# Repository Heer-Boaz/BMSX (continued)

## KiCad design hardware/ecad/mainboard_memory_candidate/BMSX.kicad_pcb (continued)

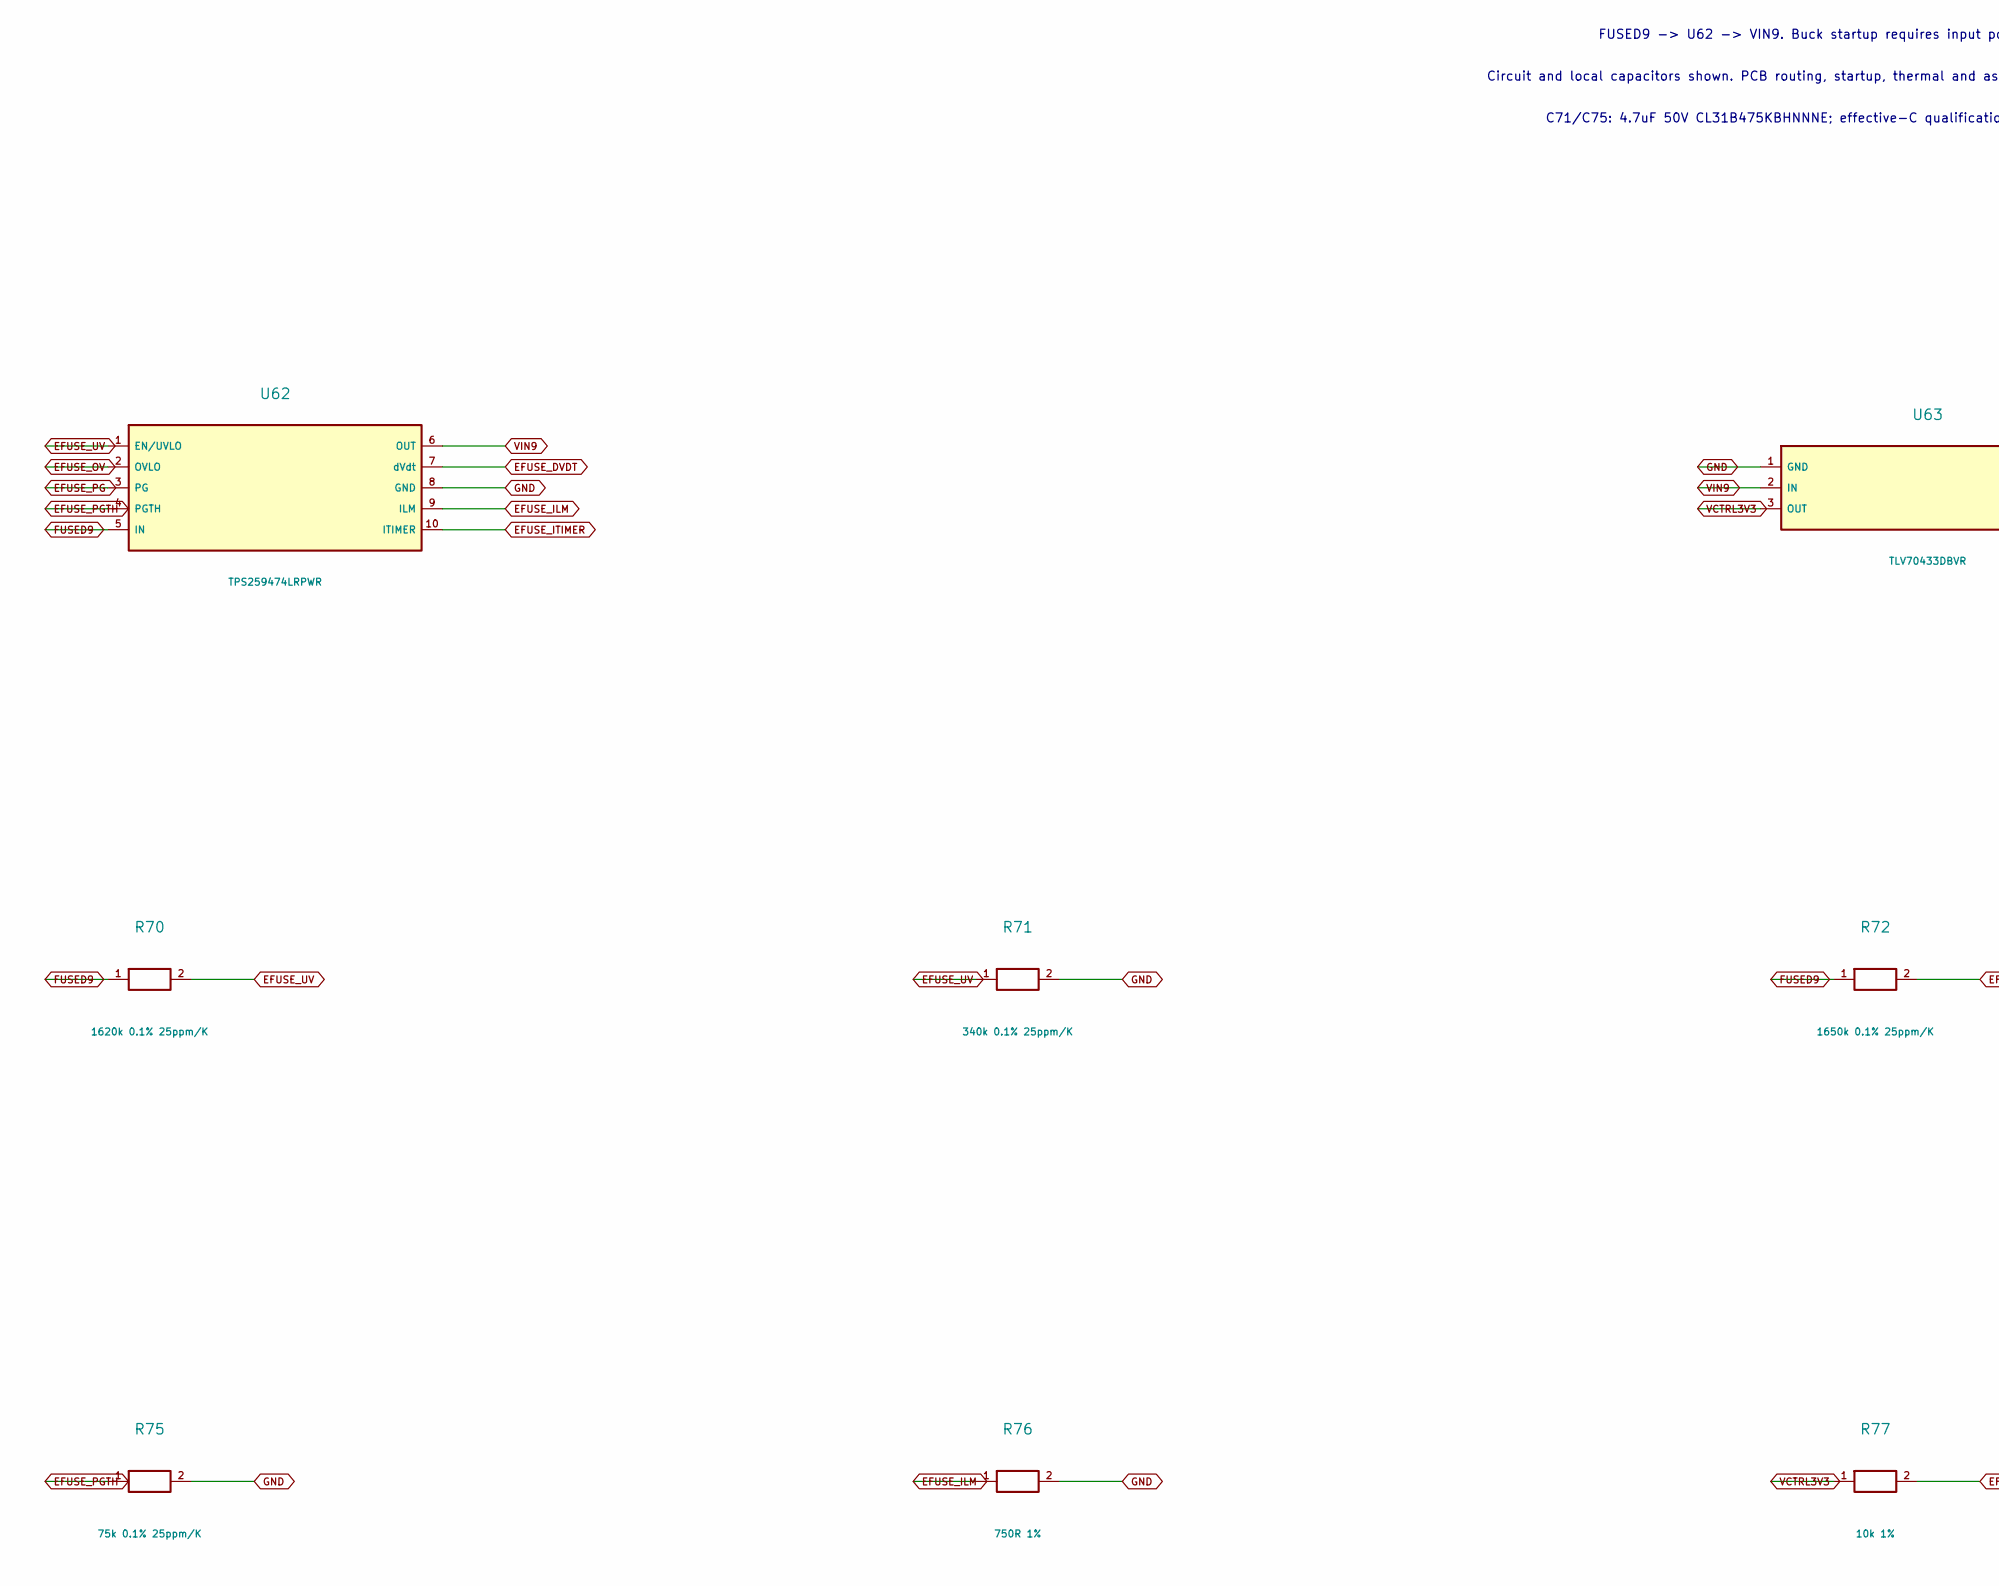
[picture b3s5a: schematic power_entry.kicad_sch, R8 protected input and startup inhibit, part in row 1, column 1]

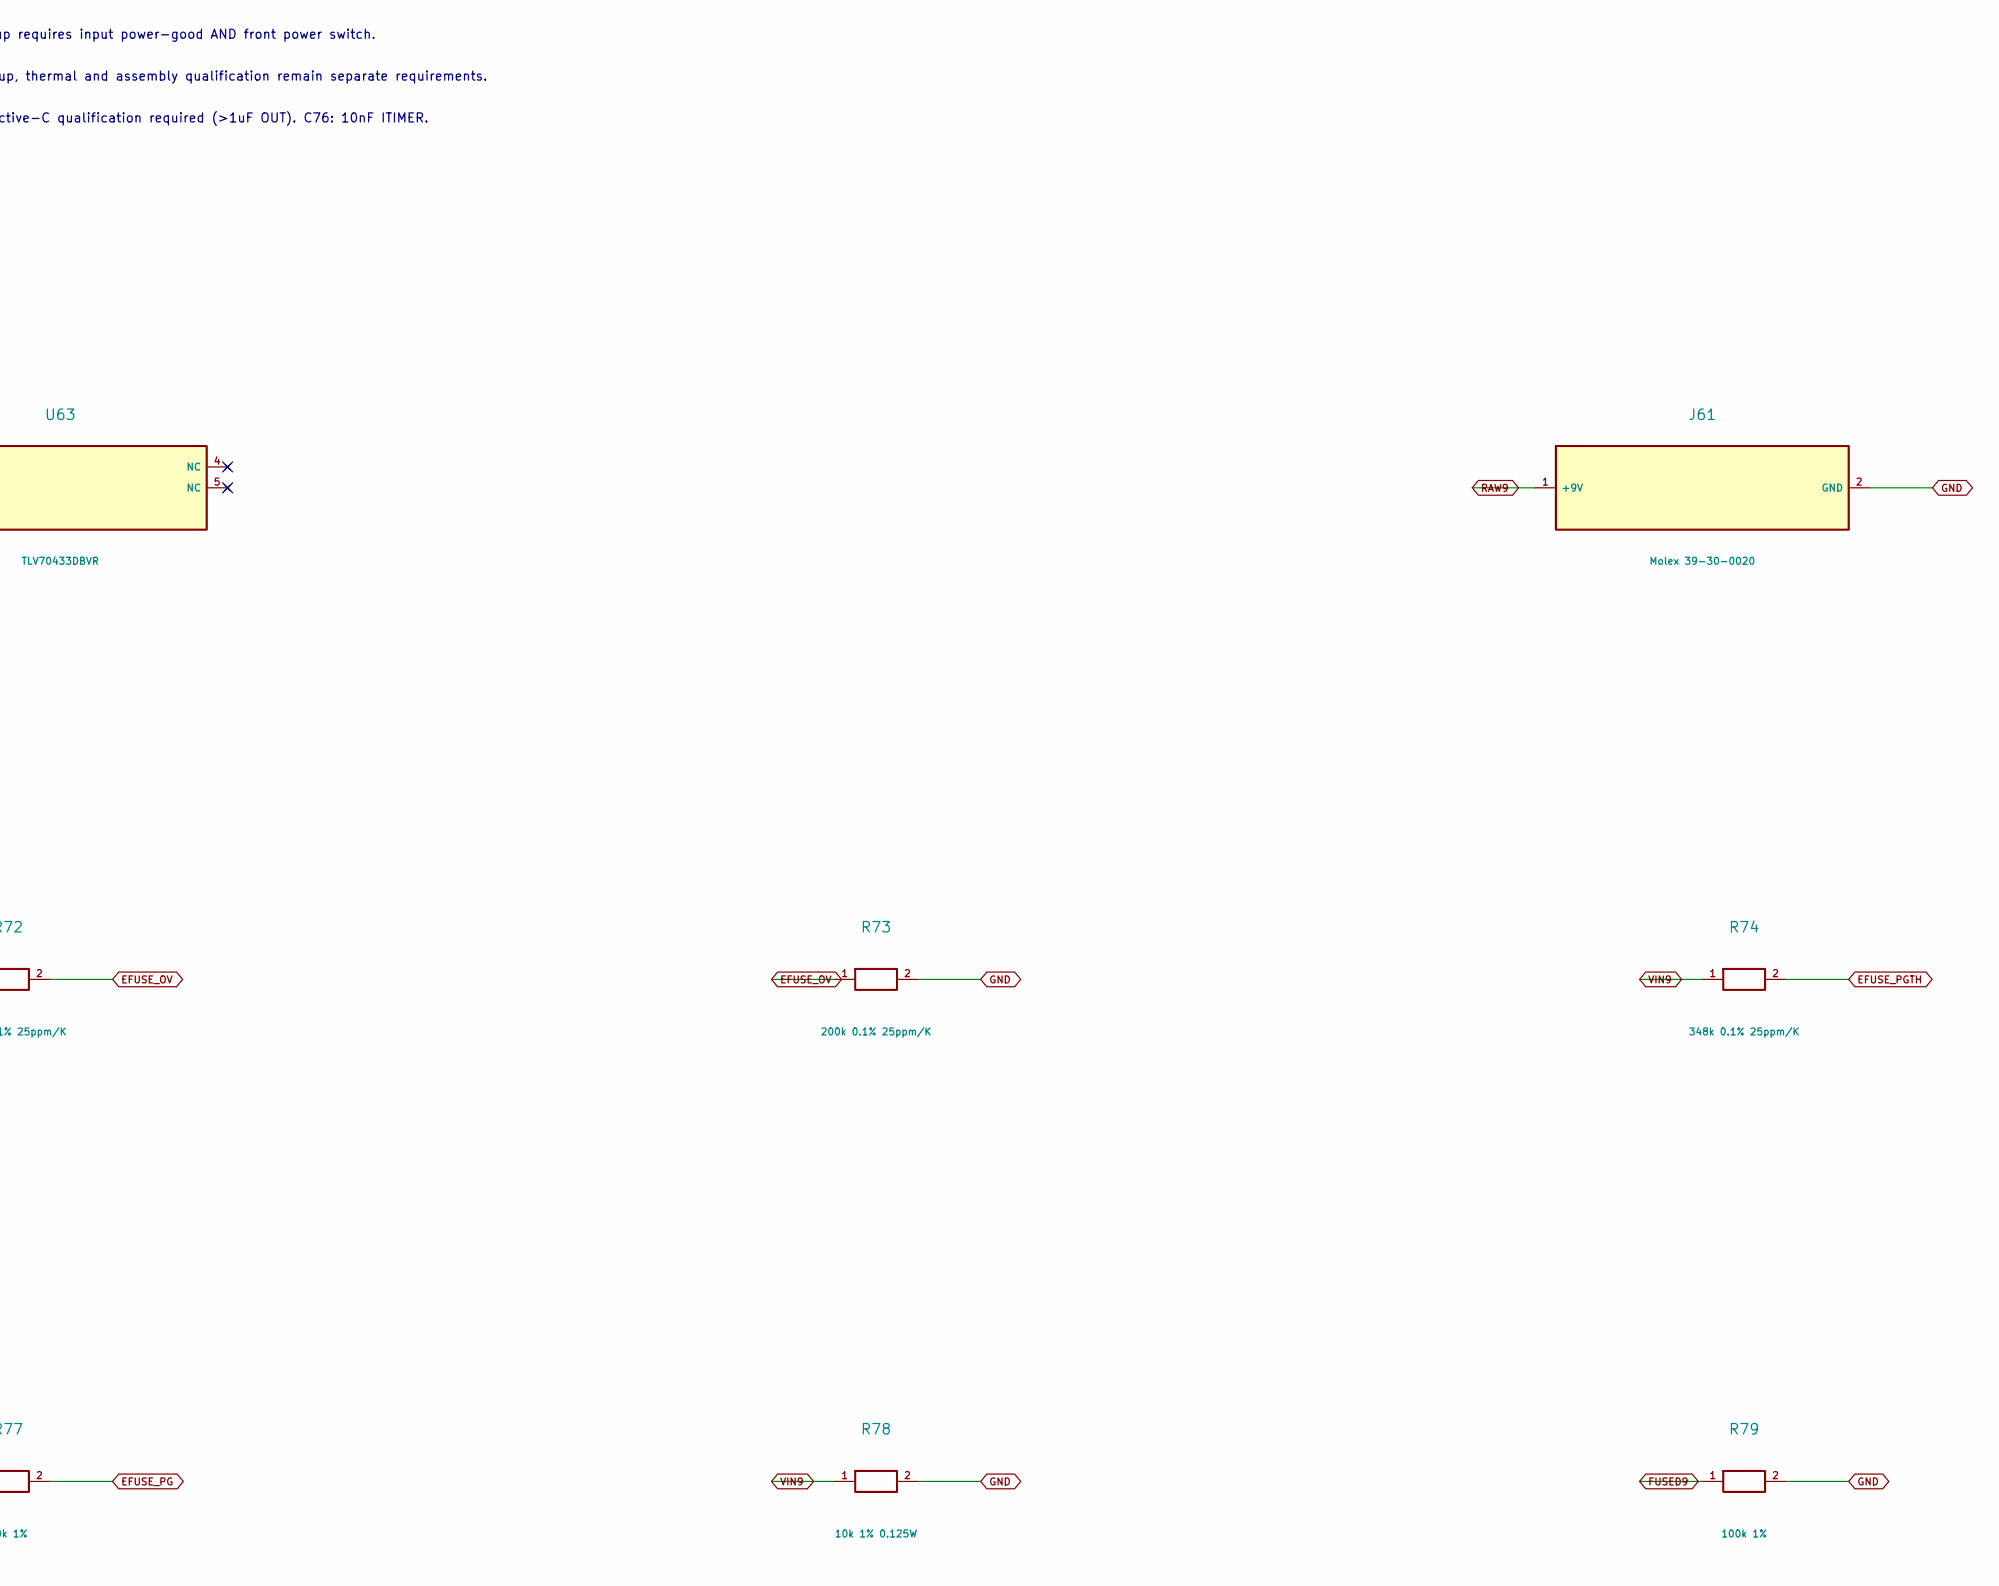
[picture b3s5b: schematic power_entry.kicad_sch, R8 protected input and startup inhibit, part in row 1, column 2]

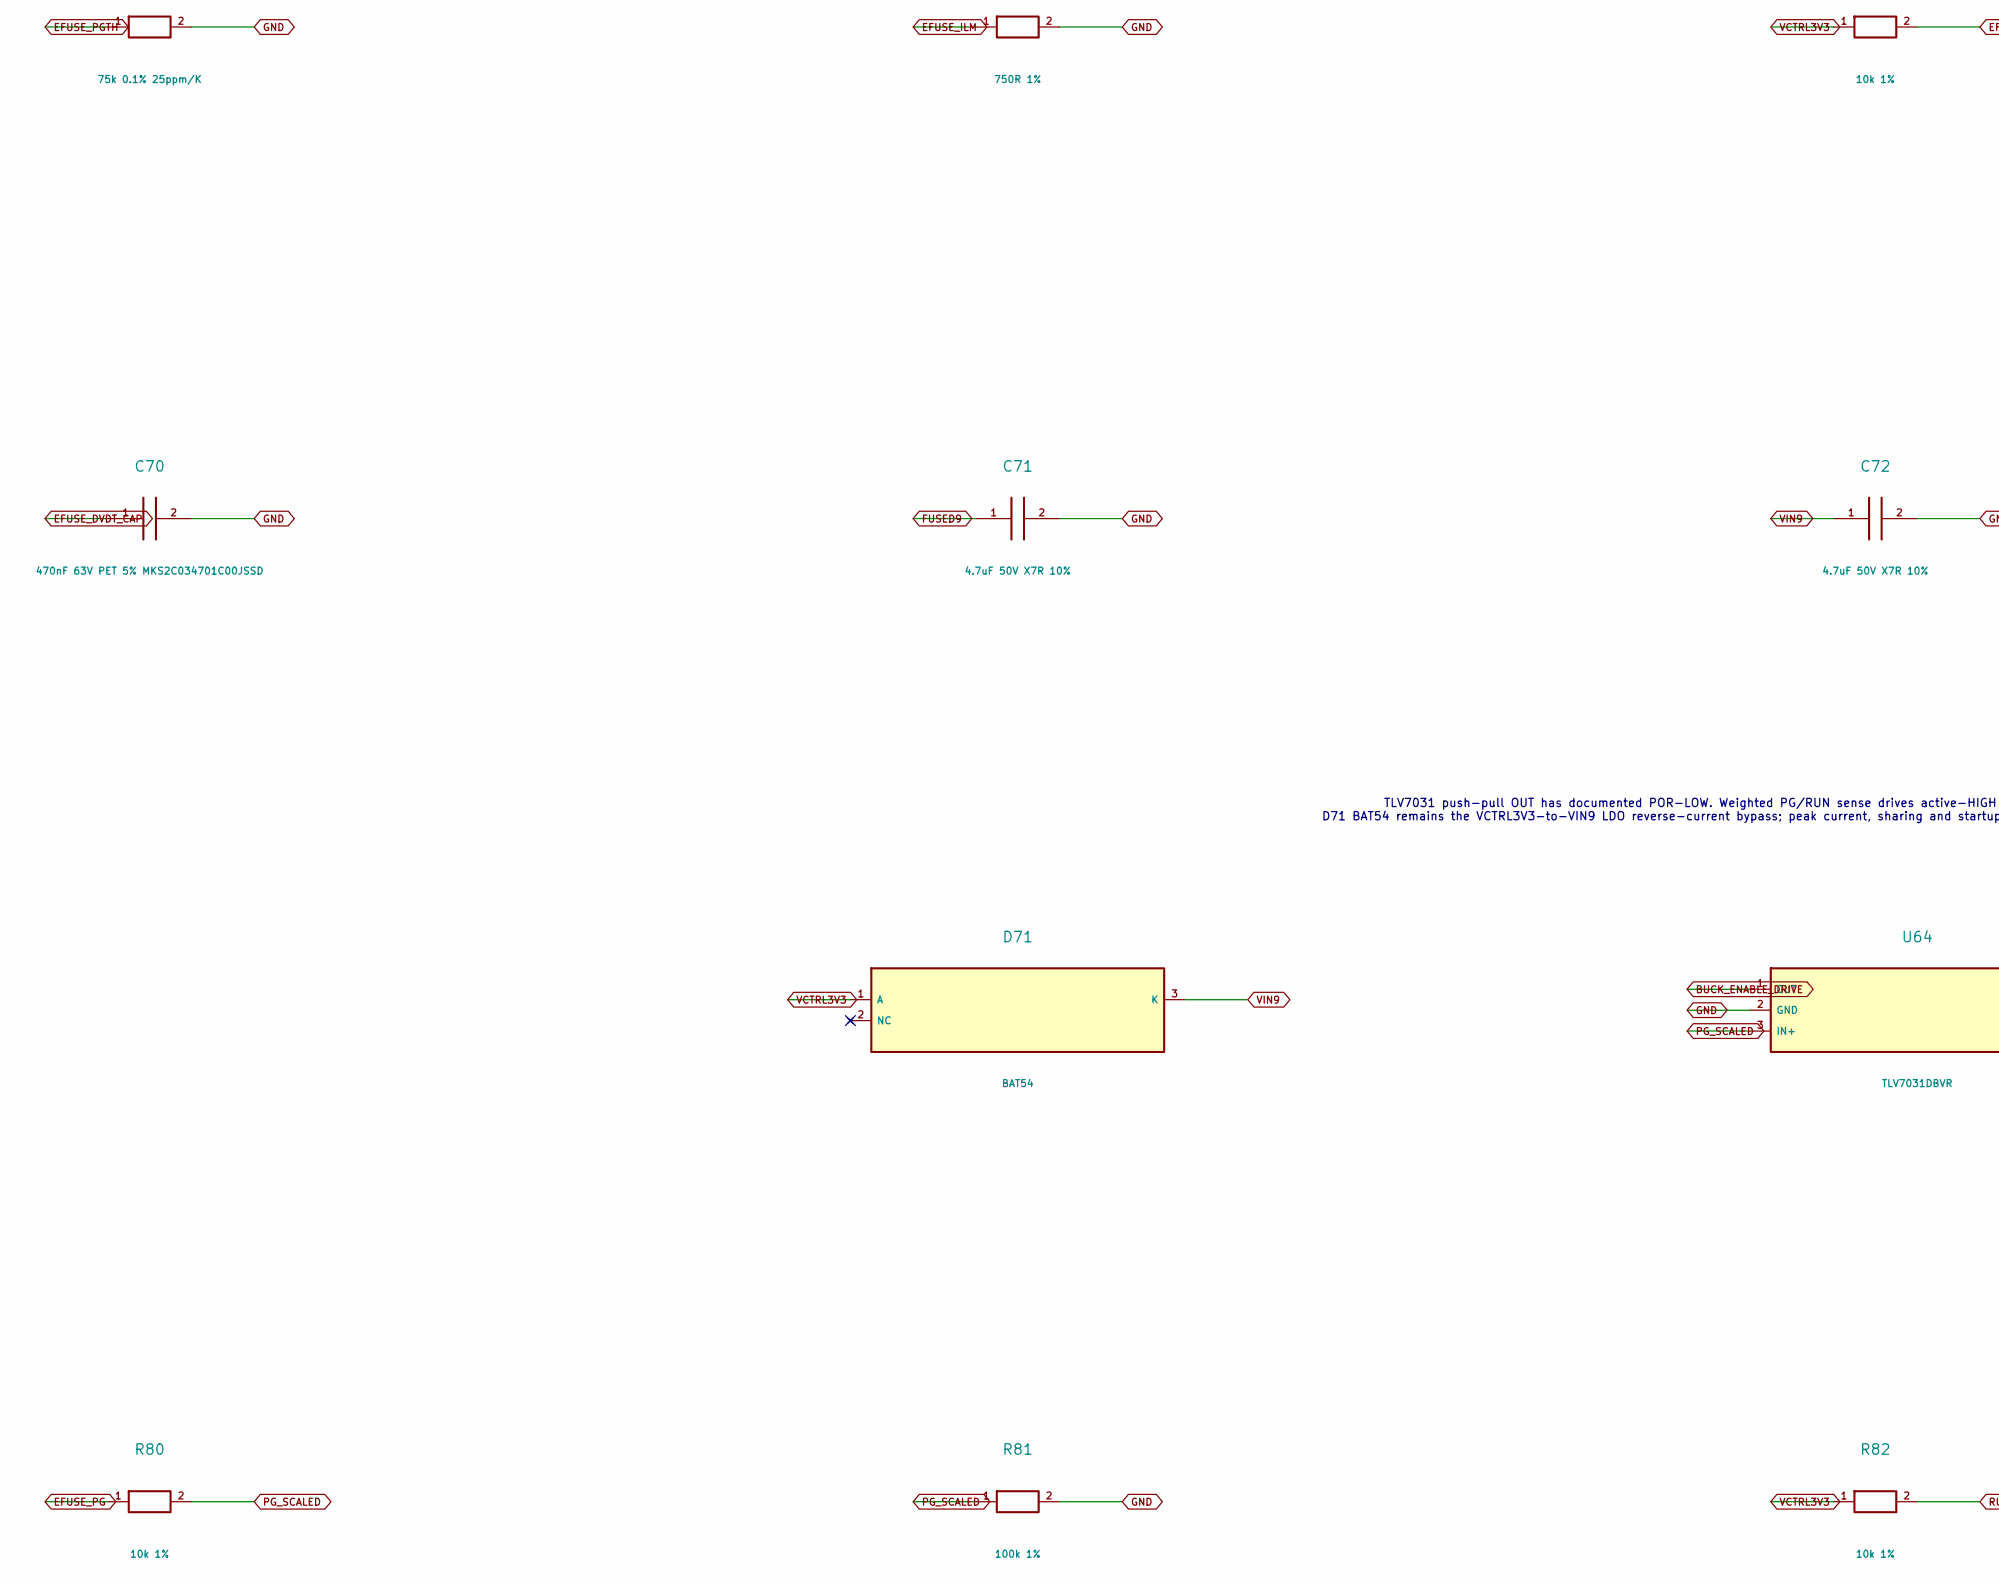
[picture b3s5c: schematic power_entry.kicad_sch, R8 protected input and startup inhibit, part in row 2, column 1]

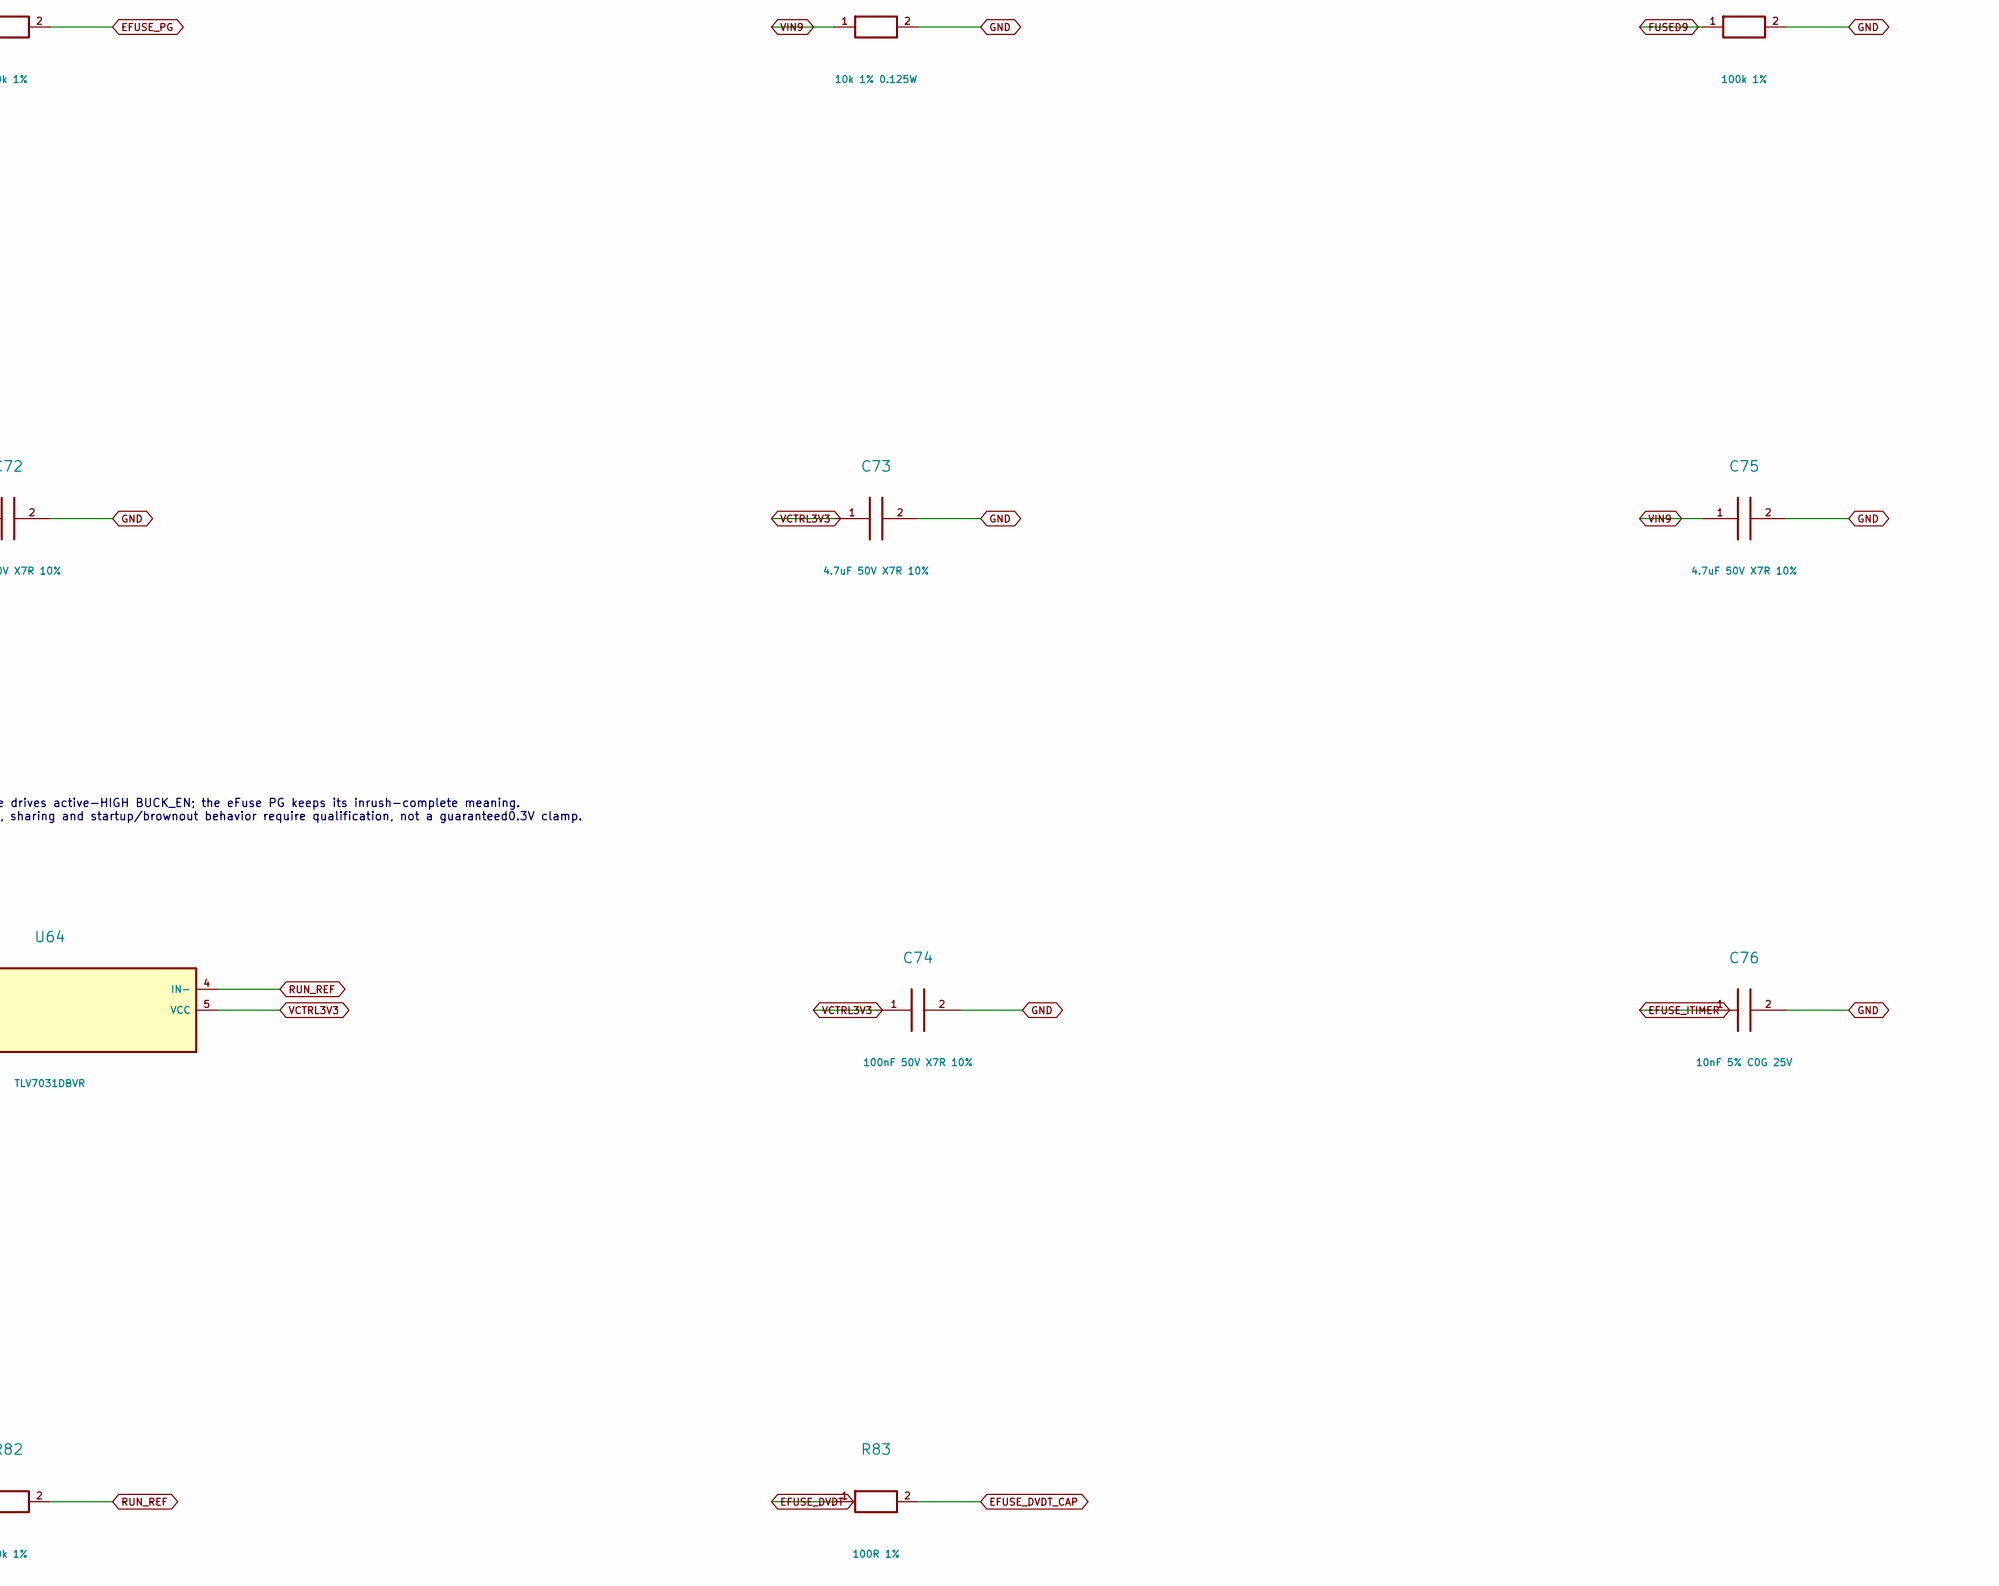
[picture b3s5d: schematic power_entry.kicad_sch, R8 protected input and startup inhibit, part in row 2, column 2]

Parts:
C70: 470nF 63V PET 5% MKS2C034701C00JSSD; MKS2C034701C00JSSD; MPN MKS2C034701C00JSSD
C71, C72, C73, C75: 4.7uF 50V X7R 10%; CL31B475KBHNNNE; MPN CL31B475KBHNNNE
C74: 100nF 50V X7R 10%; CL21B104KBCNNNC; MPN CL21B104KBCNNNC
C76: 10nF 5% C0G 25V; C76
D71: BAT54; BAT54_E3_08_SOT23; MPN BAT54-E3-08
J61: Molex 39-30-0020; J61
R70: 1620k 0.1% 25ppm/K; CPF0805_TE_1773200; MPN CPF0805B1M62E1
R71: 340k 0.1% 25ppm/K; CPF0805_TE_1773200; MPN CPF0805B340KE1
R72: 1650k 0.1% 25ppm/K; CPF0805_TE_1773200; MPN CPF0805B1M65E1
R73: 200k 0.1% 25ppm/K; CPF0805_TE_1773200; MPN CPF0805B200KE1
R74: 348k 0.1% 25ppm/K; TNPW0805_Vishay_28950; MPN TNPW0805348KBEEA
R75: 75k 0.1% 25ppm/K; TNPW0805_Vishay_28950; MPN TNPW080575K0BEEA
R76: 750R 1%; R76
R77: 10k 1%; R77; MPN RC0805FR-0710KL
R78: 10k 1% 0.125W; R78
R79: 100k 1%; R79
R80, R82: 10k 1%; Yageo_RC0805_retained_IPC; MPN RC0805FR-0710KL
R81: 100k 1%; Yageo_RC0805_retained_IPC; MPN RC0805FR-07100KL
R83: 100R 1%; R83
U62: TPS259474LRPWR; TPS259474_RPW0010A; MPN TPS259474LRPWR
U63: TLV70433DBVR; TLV70433DBVR_DBV0005A; MPN TLV70433DBVR
U64: TLV7031DBVR; TLV7031DBVR_DBV0005A; MPN TLV7031DBVR

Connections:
BUCK_ENABLE_DRIVE: U64.1 (OUT); also elsewhere on the board
EFUSE_DVDT: R83.1, U62.7 (dVdt)
EFUSE_DVDT_CAP: C70.1, R83.2
EFUSE_ILM: R76.1, U62.9 (ILM)
EFUSE_ITIMER: C76.1, U62.10 (ITIMER)
EFUSE_OV: R72.2, R73.1, U62.2 (OVLO)
EFUSE_PG: R77.2, R80.1, U62.3 (PG)
EFUSE_PGTH: R74.2, R75.1, U62.4 (PGTH)
EFUSE_UV: R70.2, R71.1, U62.1 (EN/UVLO)
FUSED9: C71.1, R70.1, R72.1, R79.1, U62.5 (IN); also elsewhere on the board
GND: C70.2, C71.2, C72.2, C73.2, C74.2, C75.2, C76.2, J61.2 (GND), R71.2, R73.2, R75.2, R76.2, R78.2, R79.2, R81.2, U62.8 (GND), U63.1 (GND), U64.2 (GND); also elsewhere on the board
PG_SCALED: R80.2, R81.1, U64.3 (IN+)
RAW9: J61.1 (+9V); also elsewhere on the board
RUN_REF: R82.2, U64.4 (IN-); also elsewhere on the board
VCTRL3V3: C73.1, C74.1, D71.1 (A), R77.1, R82.1, U63.3 (OUT), U64.5 (VCC); also elsewhere on the board
VIN9: C72.1, C75.1, D71.3 (K), R74.1, R78.1, U62.6 (OUT), U63.2 (IN); also elsewhere on the board

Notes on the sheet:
FUSED9 -> U62 -> VIN9. Buck startup requires input power-good AND front power switch.
Circuit and local capacitors shown. PCB routing, startup, thermal and assembly qualification remain separate requirements.
C71/C75: 4.7uF 50V CL31B475KBHNNNE; effective-C qualification required (>1uF OUT). C76: 10nF ITIMER.
TLV7031 push-pull OUT has documented POR-LOW. Weighted PG/RUN sense drives active-HIGH BUCK_EN; the eFuse PG keeps its inrush-complete meaning. D71 BAT54 remains the VCTRL3V3-to-VIN9 LDO reverse-current bypass; peak current, sharing and startup/brownout behavior require qualification, not a guarant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
